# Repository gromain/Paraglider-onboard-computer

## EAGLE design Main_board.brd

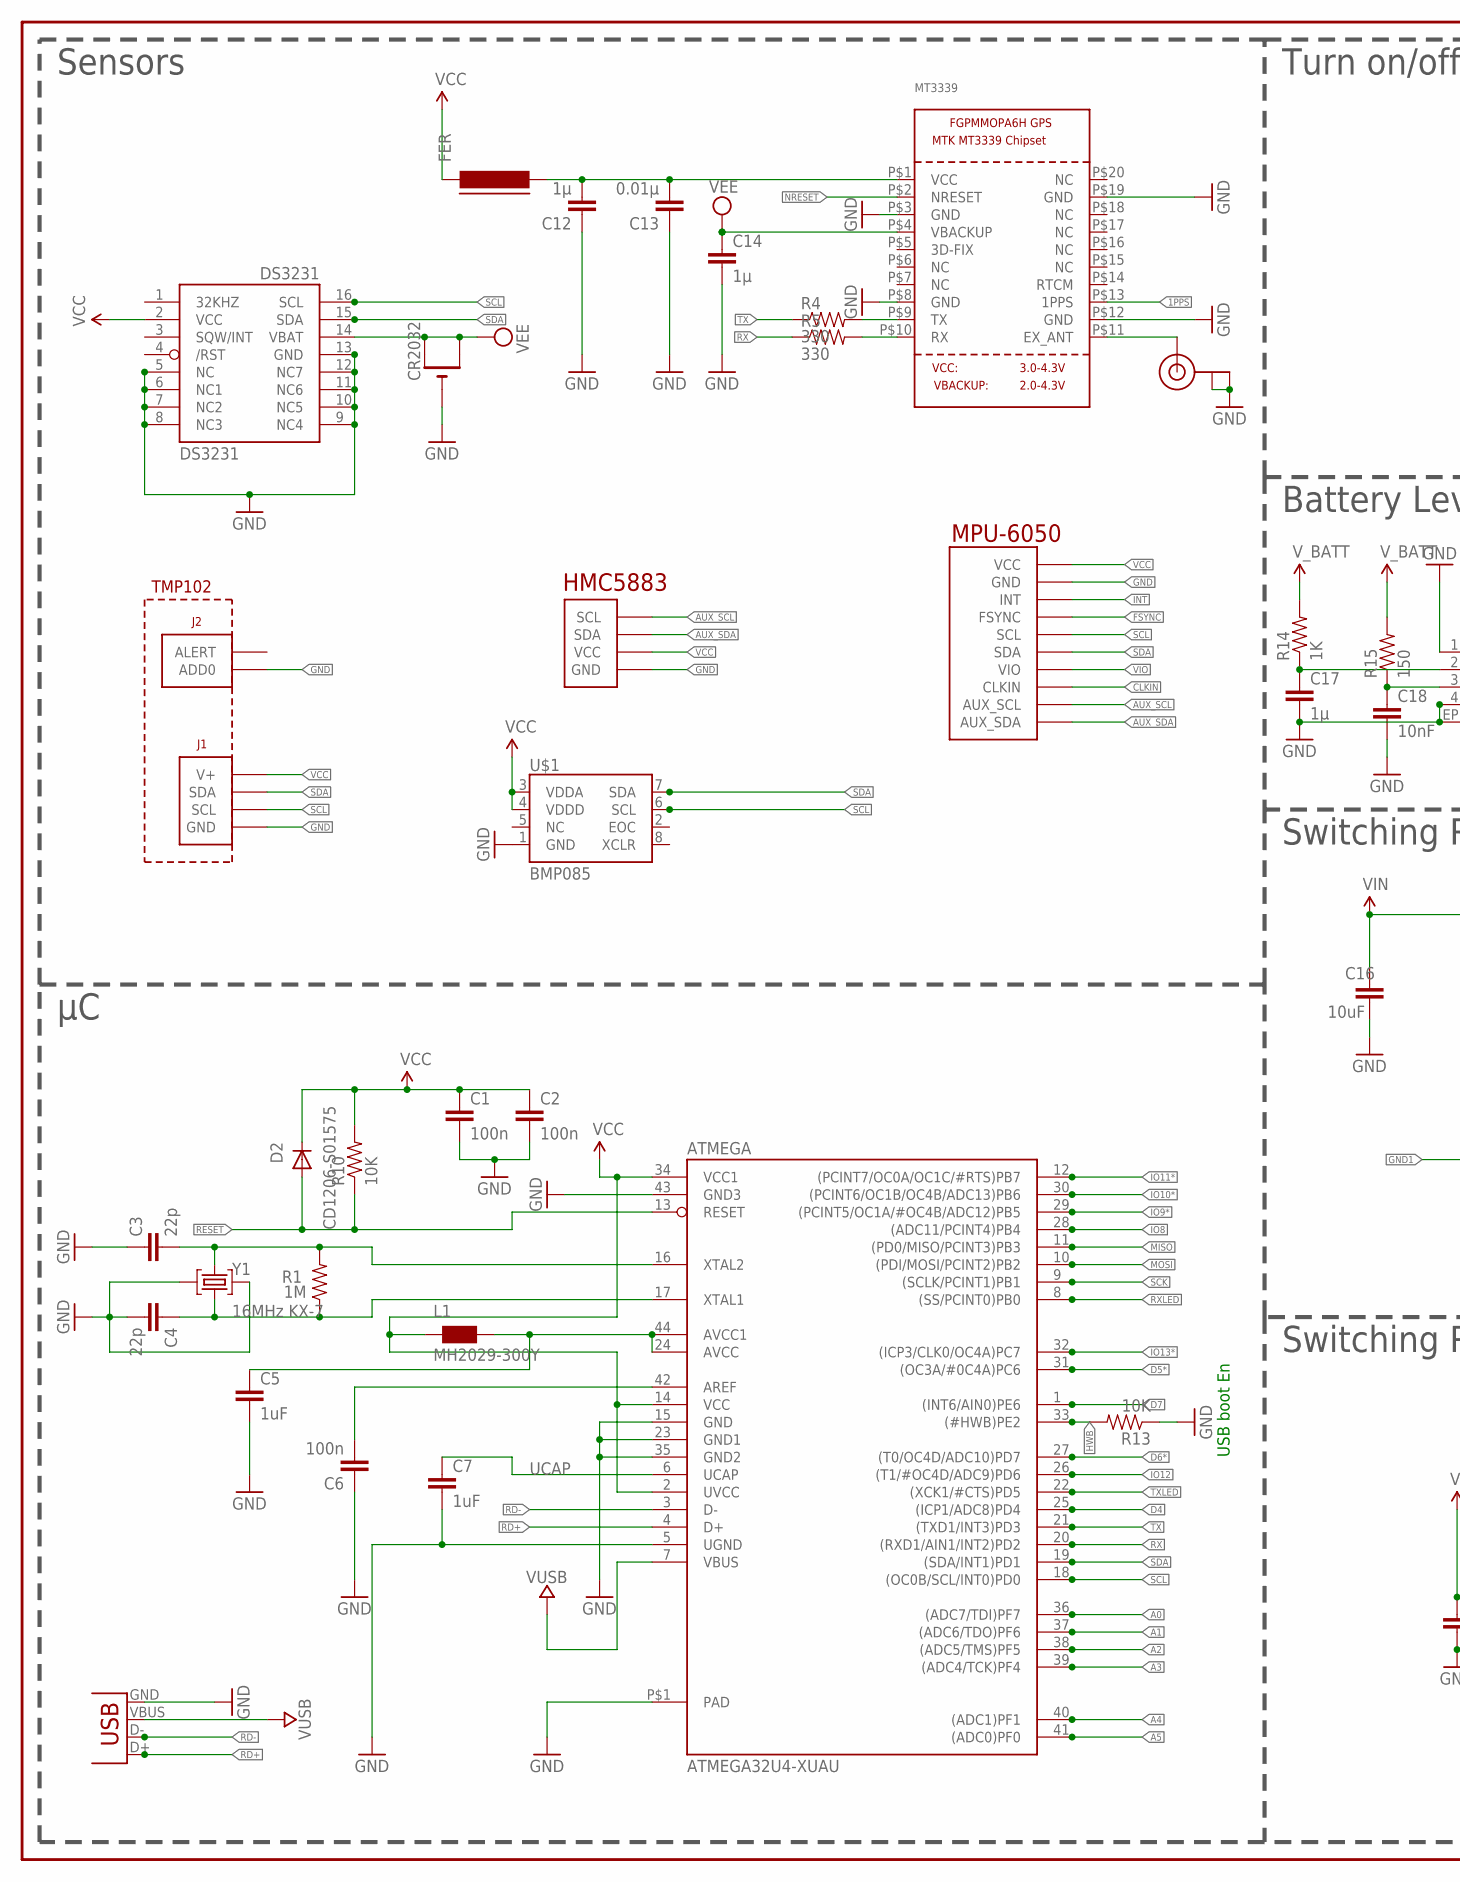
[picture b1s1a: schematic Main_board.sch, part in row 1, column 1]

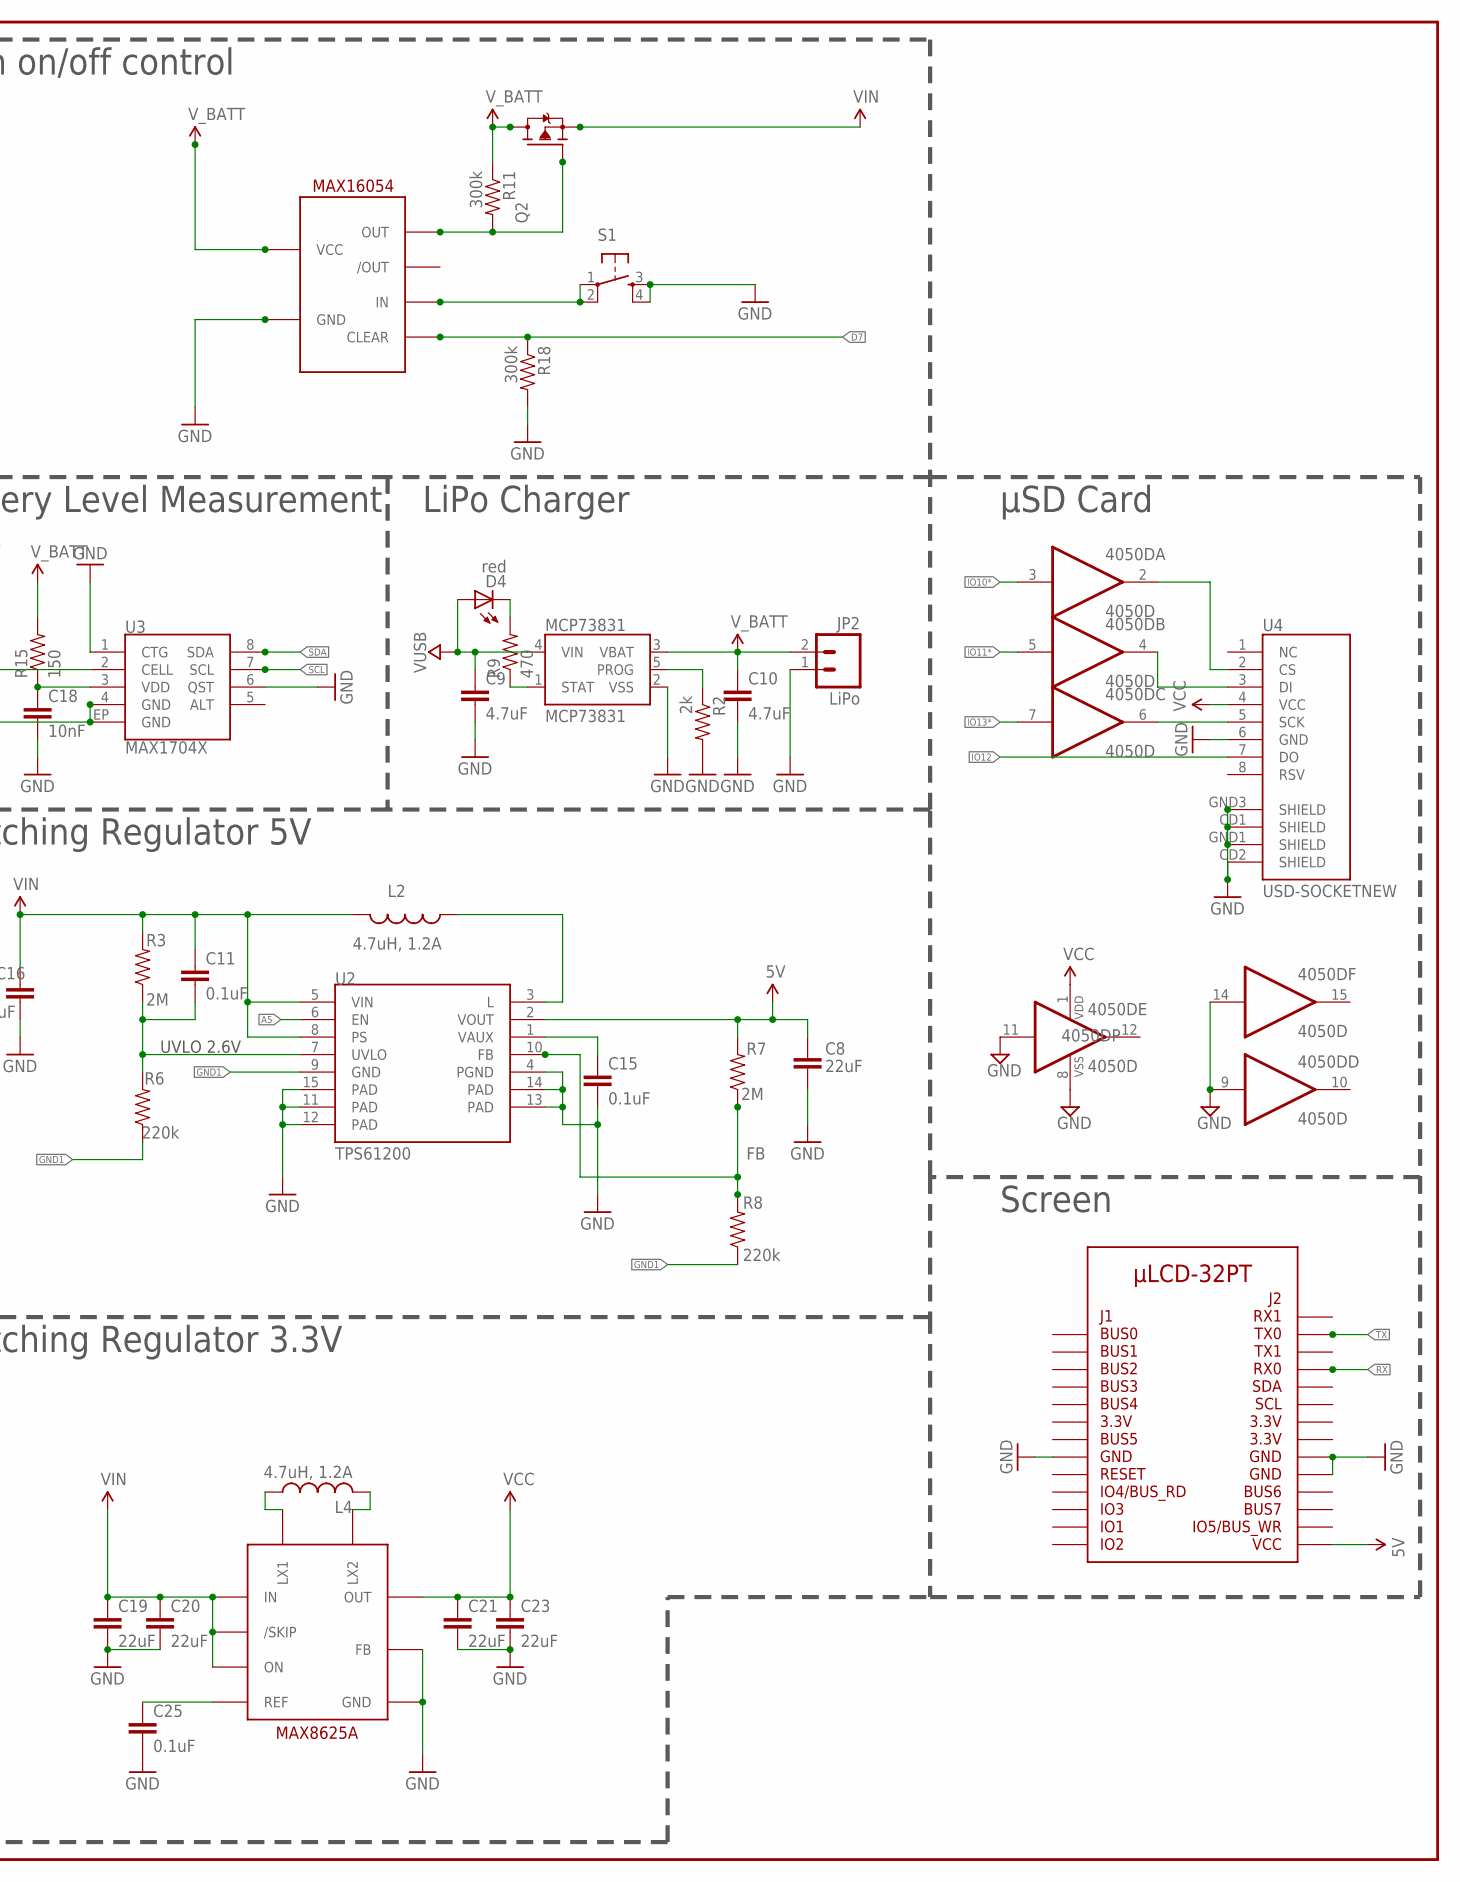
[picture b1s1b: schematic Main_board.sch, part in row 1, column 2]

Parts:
4050D: 4050D; SO16
ATMEGA: ATMEGA32U4-XUAU; TQFP44-PAD
C1, C2, C6: 100n; 0805
C3, C4: 22p; 0805
C5, C7: 1uF; 0805
C8, C19, C20, C21, C23: 22uF; 0805
C9, C10: 4.7uF; 0805
C11, C15, C25: 0.1uF; 0805
C12, C14, C17: 1µ; 0805
C13: 0.01µ; 0805
C16: 10uF; 0805
C18: 10nF; 0805
CR2032: CR2032SMT; CR2032-SMD
D2: CD1206-S01575; MINIMELF
D4: red; LED-1206
DS3231: DS3231/SO; SO16W
FER: FERRITE-1206; FB1206
JP2: LiPo; JST-2-SMD
L1: MH2029-300Y; 0805
L2, L4: 4.7uH, 1.2A; 2520
MAX16054: MAX16054; SOT23-6L
MCP73831: MCP73831; SOT23-5
MT3339: GPS_FGPMMOPA6H; FGPMMOPA6H
Q2: TRANSISTOR_FET_TSM2301CX; SOT-23
R1: 1M; 0805
R2: 2k; 0805
R3, R7: 2M; 0805
R4, R5: 330; 0805
R6, R8: 220k; 0805
R9: 470; 0805
R10, R13: 10K; 0805
R11, R18: 300k; 0805
R14: 1K; 0805
R15: 150; 0805
S1: TAC_SWITCHSMD; TACTILE_SWITCH_SMD
U2: TPS61200; QFN-10_PAD
U3: MAX1704X; TDFN-8
U4: USD-SOCKETNEW; MICRO-SD-SOCKET-PP
U$1: BMP085
U$2: µLCD-32PT
U$3: U.FL
U$6: HMC5883
U$7: MPU-6050
U$8: TMP102
U$9: MAX8625A; 14-TDFN-EP
X1: USB-MICROB
Y1: 16MHz KX-7; CRYSTAL-3.2-2.5

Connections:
1PPS: MT3339.P$13 (1PPS)
5V: C8.1, R7.2, U2.2 (VOUT), U$2.J2-P6
A0: ATMEGA.36 ((ADC7/TDI)PF7)
A1: ATMEGA.37 ((ADC6/TDO)PF6)
A2: ATMEGA.38 ((ADC5/TMS)PF5)
A3: ATMEGA.39 ((ADC4/TCK)PF4)
A4: ATMEGA.40 ((ADC1)PF1)
A5: ATMEGA.41 ((ADC0)PF0), U2.6 (EN)
AREF: ATMEGA.42 (AREF), C6.2
AUX_SCL: U$6.SCL, U$7.AUX_SCL
AUX_SDA: U$6.SDA, U$7.AUX_SDA
AVCC: ATMEGA.24 (AVCC), ATMEGA.44 (AVCC1), C5.1, L1.2
CLKIN: U$7.CLK (CLKIN)
D4: ATMEGA.25 ((ICP1/ADC8)PD4)
D5*: ATMEGA.31 ((OC3A/#0C4A)PC6)
D6*: ATMEGA.27 ((T0/OC4D/ADC10)PD7)
D7: ATMEGA.1 ((INT6/AIN0)PE6), MAX16054.3 (CLEAR), R18.1
FB: R7.1, R8.2, U2.10 (FB)
FSYNC: U$7.FSYNC
GND: 4050D.8 (VSS), 4050D.9 (I), 4050D.11 (I), 4050D.14 (I), ATMEGA.5 (UGND), ATMEGA.15 (GND), ATMEGA.23 (GND1), ATMEGA.35 (GND2), ATMEGA.43 (GND3), ATMEGA.P$1 (PAD), C1.2, C2.2, C3.1, C4.2, C5.2, C6.1, C7.2, C8.2, C9.2, C10.2, C12.1, C13.1, C14.2, C15.2, C16.2, C17.2, C18.2, C19.2, C20.2, C21.2, C23.2, C25.2, CR2032.-, DS3231.5 (NC), DS3231.6 (NC1), DS3231.7 (NC2), DS3231.8 (NC3), DS3231.9 (NC4), DS3231.10 (NC5), DS3231.11 (NC6), DS3231.12 (NC7), DS3231.13 (GND), JP2.1, MAX16054.2 (GND), MCP73831.2 (VSS), MT3339.P$3 (GND), MT3339.P$8 (GND), MT3339.P$12 (GND), MT3339.P$19 (GND), R2.2, R13.1, R18.2, S1.3, S1.4, U2.4 (PGND), U2.11 (PAD), U2.12 (PAD), U2.13 (PAD), U2.14 (PAD), U2.15 (PAD), U3.1 (CTG), U3.4 (GND), U3.6 (QST), U3.EP (GND), U4.6 (GND), U4.CD1 (SHIELD), U4.CD2 (SHIELD), U4.GND1 (SHIELD), U4.GND3 (SHIELD), U$1.1 (GND), U$2.J1-P15, U$2.J2-P15, U$2.J2-P17, U$3.P$1 (GND), U$3.P$2 (GND), U$6.GND, U$7.GND, U$8.ADD0, U$8.GND, U$9.P$8 (FB), U$9.P$12 (GND), U$9.P$13 (GND), X1.GND, Y1.2 (GND), Y1.4 (GND)
GND1: R6.1, R8.1, U2.9 (GND)
HWB: ATMEGA.33 ((#HWB)PE2), R13.2
INT: U$7.INT
IO8: ATMEGA.28 ((ADC11/PCINT4)PB4)
IO9*: ATMEGA.29 ((PCINT5/OC1A/#OC4B/ADC12)PB5)
IO10*: 4050D.3 (I), ATMEGA.30 ((PCINT6/OC1B/OC4B/ADC13)PB6)
IO11*: 4050D.5 (I), ATMEGA.12 ((PCINT7/OC0A/OC1C/#RTS)PB7)
IO12: ATMEGA.26 ((T1/#OC4D/ADC9)PD6), U4.7 (DO)
IO13*: 4050D.7 (I), ATMEGA.32 ((ICP3/CLK0/OC4A)PC7)
J1-P18: U$2.J1-P18
J2-P16: U$2.J2-P16
J2-P18: U$2.J2-P18
MISO: ATMEGA.11 ((PD0/MISO/PCINT3)PB3)
MOSI: ATMEGA.10 ((PDI/MOSI/PCINT2)PB2)
unnamed: MT3339.P$11 (EX_ANT), U$3.P$3 (SIGNAL)
unnamed: D4.C, R9.2
unnamed: L2.P$1 (1), U2.3 (L)
unnamed: C15.1, U2.1 (VAUX)
unnamed: C17.1, R14.1, U3.2 (CELL)
unnamed: 4050D.4 (O), U4.3 (DI)
unnamed: MT3339.P$9 (TX), R4.2
unnamed: MT3339.P$10 (RX), R5.2
unnamed: C12.2, C13.2, FER.2, MT3339.P$1 (VCC)
unnamed: C18.1, R15.1, U3.3 (VDD)
unnamed: MCP73831.5 (PROG), R2.1
unnamed: 4050D.6 (O), U4.5 (SCK)
unnamed: 4050D.2 (O), U4.2 (CS)
unnamed: MCP73831.1 (STAT), R9.1
unnamed: MAX16054.1 (IN), S1.1, S1.2
unnamed: C25.1, U$9.P$9 (REF)
unnamed: L4.P$1 (1), U$9.P$2 (LX1), U$9.P$3 (LX1)
unnamed: L4.P$2 (2), U$9.P$4 (LX2), U$9.P$5 (LX2)
NRESET: MT3339.P$2 (NRESET)
RD+: ATMEGA.4 (D+), X1.D+
RD-: ATMEGA.3 (D-), X1.D-
RESET: ATMEGA.13 (RESET), D2.A, R10.1
RX: ATMEGA.20 ((RXD1/AIN1/INT2)PD2), R5.1, U$2.J2-P27
RXLED: ATMEGA.8 ((SS/PCINT0)PB0)
SCK: ATMEGA.9 ((SCLK/PCINT1)PB1)
SCL: ATMEGA.18 ((OC0B/SCL/INT0)PD0), DS3231.16 (SCL), U3.7 (SCL), U$1.6 (SCL), U$7.SCL, U$8.SCL
SDA: ATMEGA.19 ((SDA/INT1)PD1), DS3231.15 (SDA), U3.8 (SDA), U$1.7 (SDA), U$7.SDA, U$8.SDA
TX: ATMEGA.21 ((TXD1/INT3)PD3), R4.1, U$2.J2-P29
TXLED: ATMEGA.22 ((XCK1/#CTS)PD5)
UCAP: ATMEGA.6 (UCAP), C7.1
UVLO: C11.2, R3.1, R6.2, U2.7 (UVLO)
VCC: 4050D.1 (VDD), ATMEGA.2 (UVCC), ATMEGA.14 (VCC), ATMEGA.34 (VCC1), C1.1, C2.1, C21.1, C23.1, D2.C, DS3231.2 (VCC), FER.1, L1.1, R10.2, U4.4 (VCC), U$1.3 (VDDA), U$1.4 (VDDD), U$6.VCC, U$7.VDD (VCC), U$8.V+, U$9.P$10 (OUT), U$9.P$11 (OUT)
VEE: C14.1, CR2032.+$1 (+), CR2032.+$2 (+1), DS3231.14 (VBAT), MT3339.P$4 (VBACKUP)
VIN: C11.1, C16.1, C19.1, C20.1, L2.P$2 (2), Q2.2 (S), R3.2, U2.5 (VIN), U2.8 (PS), U$9.P$6 (ON), U$9.P$7 (/SKIP), U$9.P$14 (IN), U$9.P$15 (IN)
VIO: U$7.VIO
VUSB: ATMEGA.7 (VBUS), C9.1, D4.A, MCP73831.4 (VIN), X1.VBUS
V_BATT: C10.1, JP2.2, MAX16054.6 (VCC), MCP73831.3 (VBAT), Q2.3 (D), R11.1, R14.2, R15.2
V_CTRL: MAX16054.5 (OUT), Q2.1 (G), R11.2
XTAL1: ATMEGA.17 (XTAL1), C4.1, R1.1, Y1.1 (C1)
XTAL2: ATMEGA.16 (XTAL2), C3.2, R1.2, Y1.3 (C2)

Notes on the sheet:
USB boot En
UVLO 2.6V
LiPo Charger
Switching Regulator 5V
µSD Card
Battery Level Measurement
Turn on/off control
Sensors
Switching Regulator 3.3V
Screen

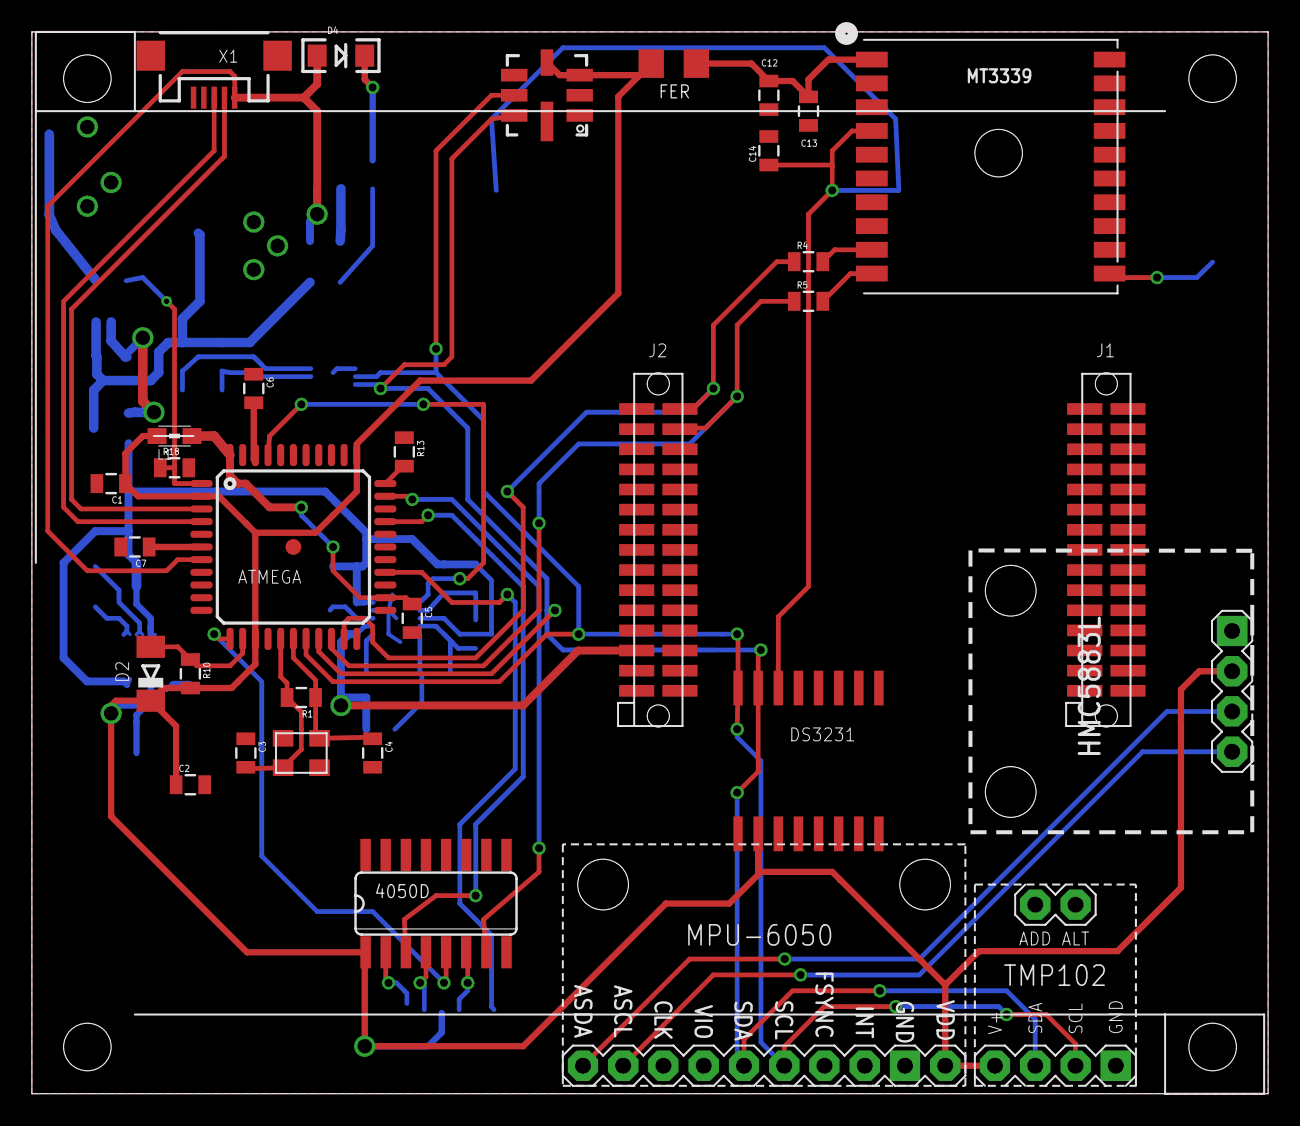
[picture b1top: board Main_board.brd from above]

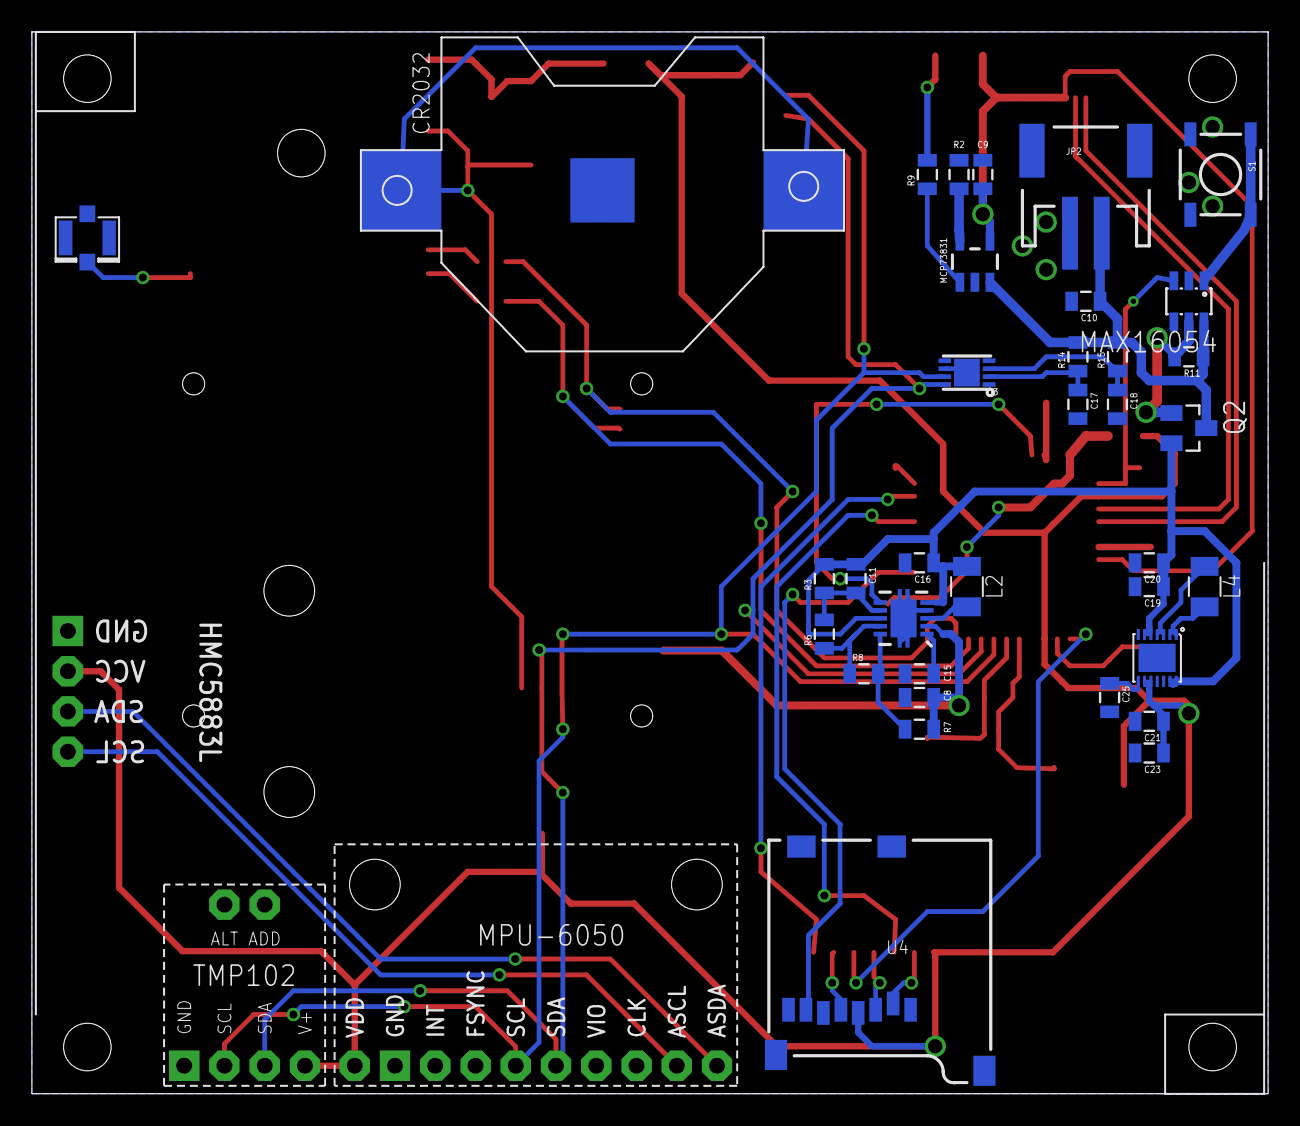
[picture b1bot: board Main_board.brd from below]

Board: 2 copper layers, 78.0 x 67.0 mm, 66 parts (35 on the bottom side), 50 nets.

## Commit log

2012-11-13 Initial release
2012-11-14 ON/OFF control added
    Via momentanary switch, with microcontroller controlled shutdown.
2012-11-15 Clean up of schematics
    General clean up + 5V reg added + On/off control connected
2012-11-15 Big update
    Replacement of old file by only one unique file
    Reorganisation of schematics
    Integration of the screen footprint
2012-11-15 Final design
    Board routed and schematics finalised and cleaned
2012-11-15 Board clean up
2012-11-22 Added cost and changes planned to circuit
    ON/OFF Circuit use to lower cost
2012-11-28 Maxim library update + ON/OFF switch mod
2012-11-28 3V3 boost converter replacement
2012-11-29 Board routing + cleaning
2013-01-28 Update to board
    Alignement to grid, and thickness of traces adjuted

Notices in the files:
parts and their libraries:
SparkFun: Licensing: CC v3.0 Share-Alike You are welcome to use this library for commercial purposes.
